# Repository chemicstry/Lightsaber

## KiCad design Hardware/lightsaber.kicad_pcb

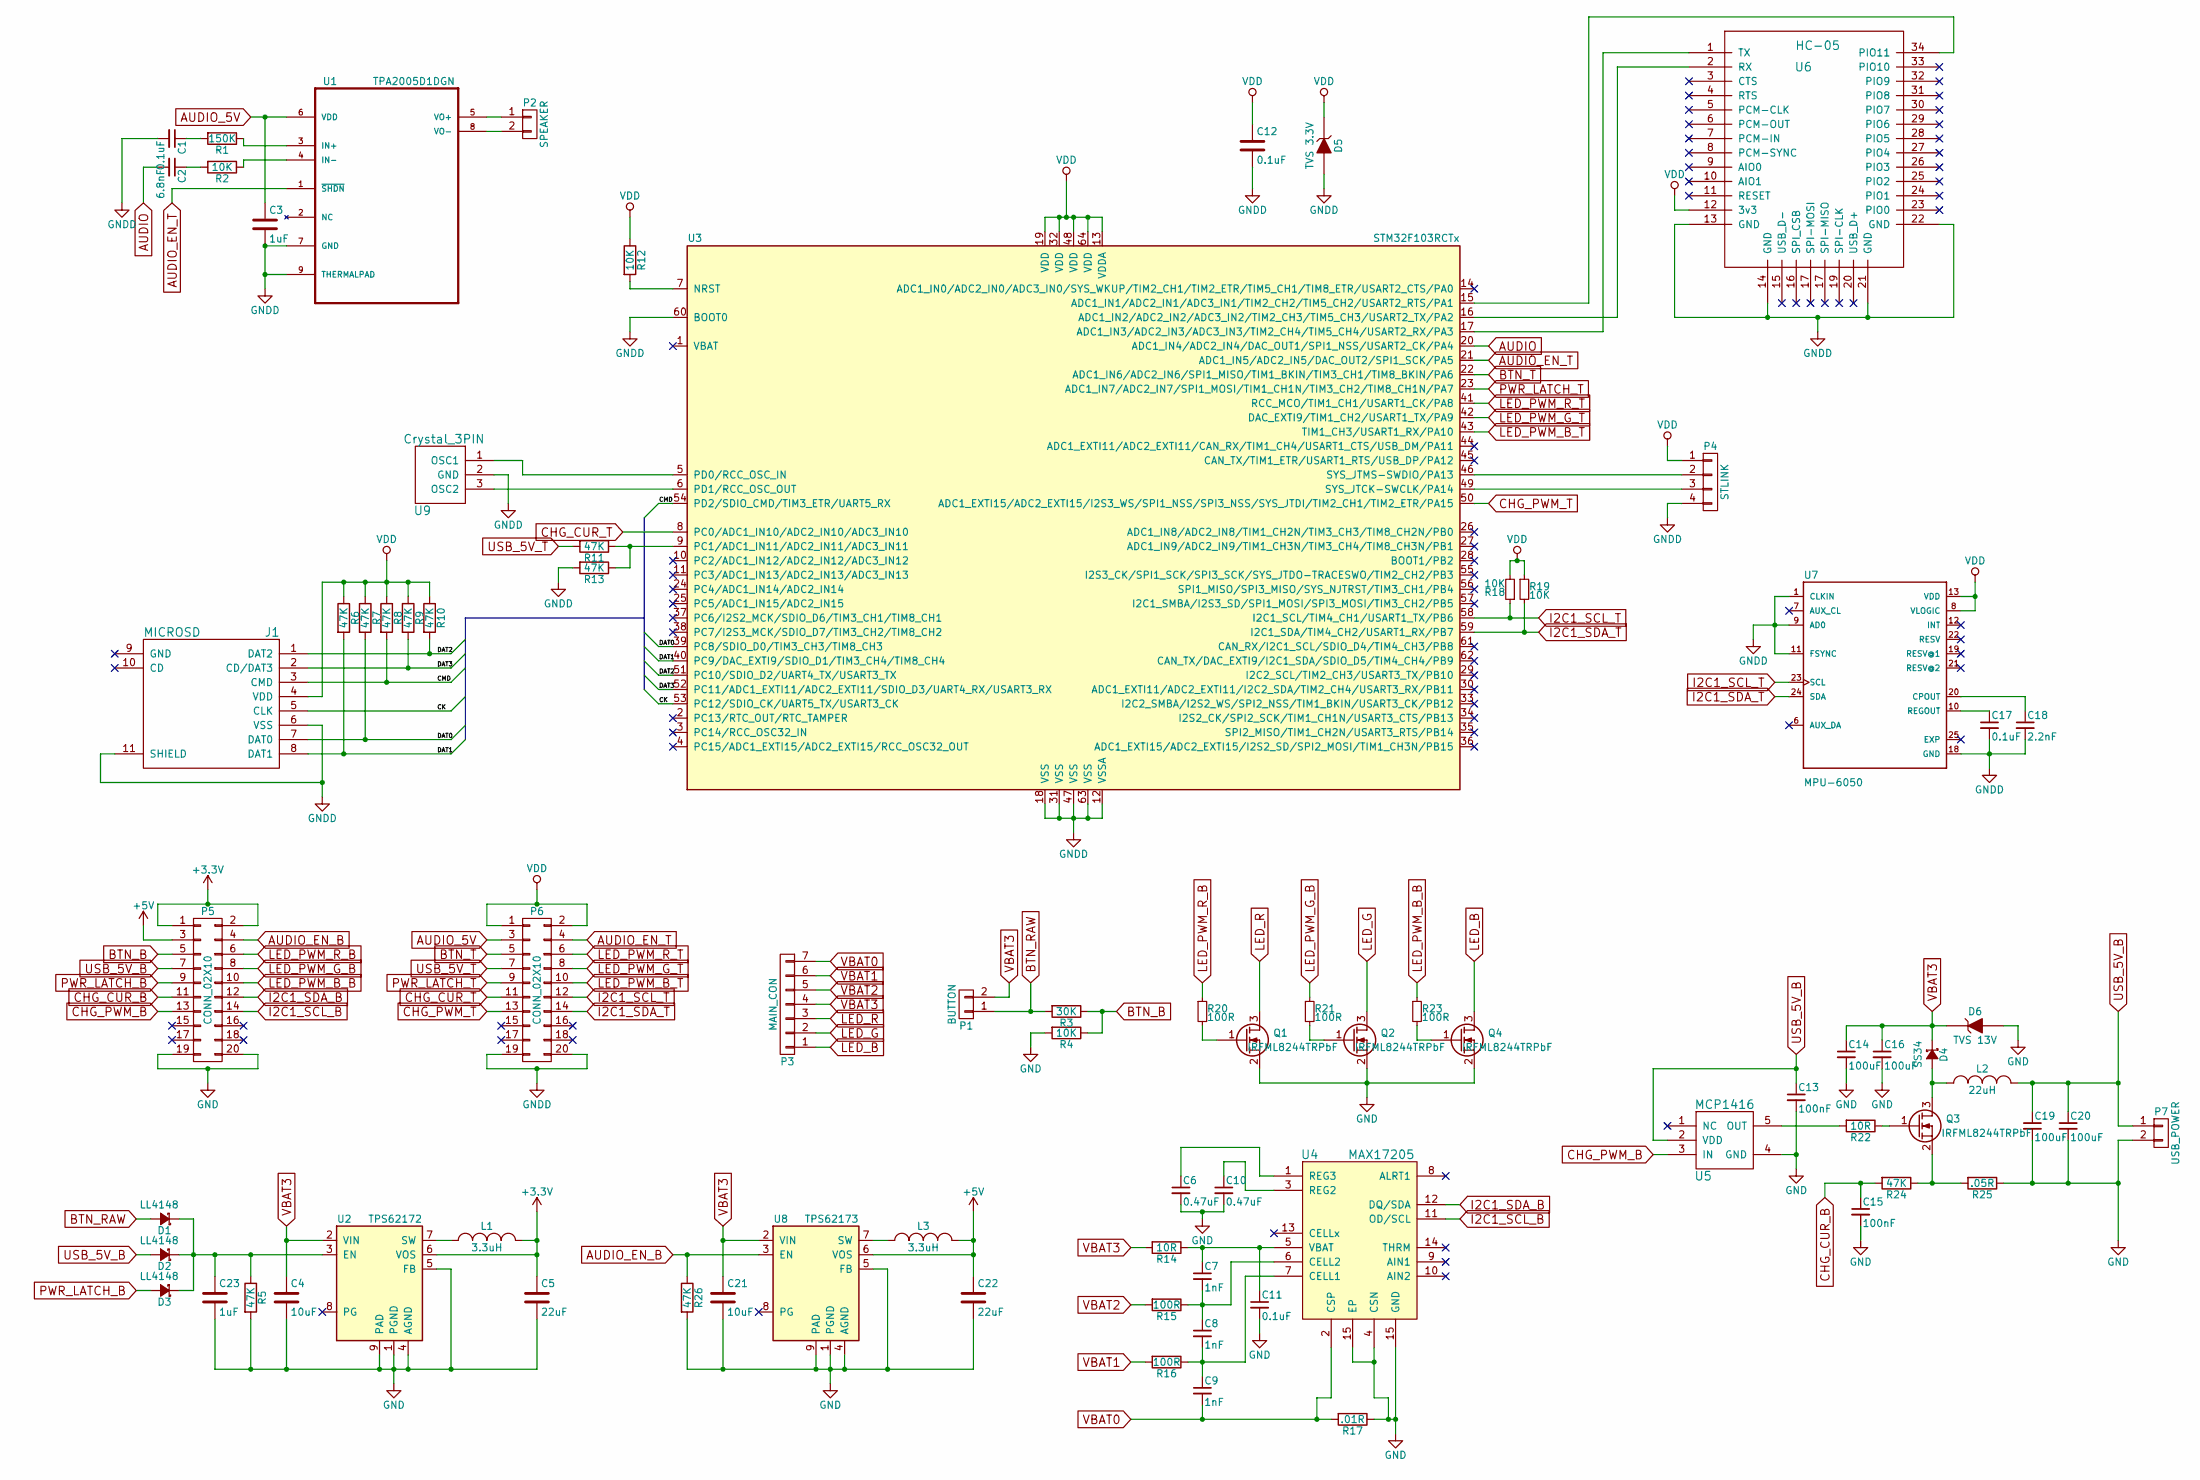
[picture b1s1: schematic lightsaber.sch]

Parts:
C1, C11, C12, C17: 0.1uF; C_0805_HandSoldering
C2: 6.8nF; C_0805_HandSoldering
C3, C23: 1uF; C_0805_HandSoldering
C4, C21: 10uF; C_0805_HandSoldering
C5, C22: 22uF; C_0805_HandSoldering
C6, C10: 0.47uF; C_0805_HandSoldering
C7, C8, C9: 1nF; C_0805_HandSoldering
C13, C15: 100nF; C_0805_HandSoldering
C14, C16, C19, C20: 100uF; C_1206_HandSoldering
C18: 2.2nF; C_0805_HandSoldering
D1, D2, D3: LL4148; SOD-80
D4: SS34; SMA-SMB_Universal_Handsoldering
D5: TVS 3.3V; D_SMB_Handsoldering
D6: TVS 13V; D_SMB_Handsoldering
J1: MICROSD; SD_CARD-112l-TXAO-R
L1, L3: 3.3uH; CD32
L2: 22uH; CD127
P1: BUTTON; JST_SH_SM02B-SRSS-TB_02x1.00mm_Angled
P2: SPEAKER; JST_SH_SM02B-SRSS-TB_02x1.00mm_Angled
P3: MAIN_CON; Pin_Header_Straight_1x07
P4: STLINK; JST_SH_BM04B-SRSS-TB_04x1.00mm_Straight
P5: CONN_02X10; PIN_HEADER_2x10_SMD_FEMALE
P6: CONN_02X10; PIN_HEADER_2x10_SMD_MALE
P7: USB_POWER; JST_PH_S2B-PH-K_02x2.00mm_Angled
Q1, Q2, Q3, Q4: IRFML8244TRPbF; SOT-23
R1: 150K; R_0805_HandSoldering
R2, R4, R12, R18, R19: 10K; R_0805_HandSoldering
R3: 30K; R_0805_HandSoldering
R5, R6, R7, R8, R9, R10, R11, R13, R24, R26: 47K; R_0805_HandSoldering
R14, R22: 10R; R_0805_HandSoldering
R15, R16, R20, R21, R23: 100R; R_0805_HandSoldering
R17: .01R; R_1206_HandSoldering
R25: .05R; R_1206_HandSoldering
U1: TPA2005D1DGN; SOP65P488X107-9N
U2: TPS62172; WSON8
U3: STM32F103RCTx; LQFP-64_10x10mm_Pitch0.5mm
U4: MAX17205; TDFN-14-1EP_3x3mm_Pitch0.4mm
U5: MCP1416; SOT-23-5
U6: HC-05
U7: MPU-6050; QFN50P400X400X95-25N
U8: TPS62173; WSON8
U9: Crystal_3PIN; Murata_CSTCE

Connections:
+3V3: C5.1, L1.2, P5.1, P5.2, U2.6 (VOS)
+5V: C22.1, L3.2, P5.3, U8.6 (VOS)
/CK: J1.5 (CLK), U3.53 (PC12/SDIO_CK/UART5_TX/USART3_CK)
/CMD: J1.3 (CMD), R8.2, U3.54 (PD2/SDIO_CMD/TIM3_ETR/UART5_RX)
/DAT0: J1.7 (DAT0), R7.2, U3.39 (PC8/SDIO_D0/TIM3_CH3/TIM8_CH3)
/DAT1: J1.8 (DAT1), R6.2, U3.40 (PC9/DAC_EXTI9/SDIO_D1/TIM3_CH4/TIM8_CH4)
/DAT2: J1.1 (DAT2), R10.2, U3.51 (PC10/SDIO_D2/UART4_TX/USART3_TX)
/DAT3: J1.2 (CD/DAT3), R9.2, U3.52 (PC11/ADC1_EXTI11/ADC2_EXTI11/SDIO_D3/UA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)
AUDIO: C2.2, U3.20 (ADC1_IN4/ADC2_IN4/DAC_OUT1/SPI1_NSS/USA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)
AUDIO_5V: C3.1, P6.3, U1.6 (VDD)
AUDIO_EN_B: P5.4, R26.1, U8.3 (EN)
AUDIO_EN_T: P6.4, U1.1 (~SHDN), U3.21 (ADC1_IN5/ADC2_IN5/DAC_OUT2/SPI1_SCK/PA5)
BTN_B: P5.5, R3.1, R4.1
BTN_RAW: D1.2 (A), P1.1, R3.2
BTN_T: P6.5, U3.22 (ADC1_IN6/ADC2_IN6/SPI1_MISO/TIM1_BKIN/T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)
CHG_CUR_B: C15.1, P5.11, R24.2
CHG_CUR_T: P6.11, U3.8 (PC0/ADC1_IN10/ADC2_IN10/ADC3_IN10)
CHG_PWM_B: P5.13, U5.3 (IN)
CHG_PWM_T: P6.13, U3.50 (ADC1_EXTI15/ADC2_EXTI15/I2S3_WS/SPI1_NS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)
GND: C4.2, C5.2, C6.2, C10.2, C11.2, C13.2, C14.2, C15.2, C16.2, C19.2, C20.2, C21.2, C22.2, C23.2, D6.2 (A), P5.19, P5.20, P7.2, Q1.2 (S), Q2.2 (S), Q4.2 (S), R4.2, R5.2, R17.1, R25.1, R26.2, U2.1 (PGND), U2.4 (AGND), U2.5 (FB), U2.9 (PAD), U4.4 (CSN), U4.15 (EP), U5.4 (GND), U8.1 (PGND), U8.4 (AGND), U8.5 (FB), U8.9 (PAD)
GNDD: C1.2, C3.2, C12.2, C17.2, C18.2, D5.2 (A), J1.6 (VSS), J1.11 (SHIELD), P4.4, P6.19, P6.20, R13.2, U1.7 (GND), U1.9 (THERMALPAD), U3.12 (VSSA), U3.18 (VSS), U3.31 (VSS), U3.47 (VSS), U3.60 (BOOT0), U3.63 (VSS), U6.13 (GND), U6.14 (GND), U6.21 (GND), U6.22 (GND), U7.1 (CLKIN), U7.9 (AD0), U7.11 (FSYNC), U7.18 (GND), U9.2 (GND)
I2C1_SCL_B: P5.14, U4.11 (OD/SCL)
I2C1_SCL_T: P6.12, R18.1, U3.58 (I2C1_SCL/TIM4_CH1/USART1_TX/PB6), U7.23 (SCL)
I2C1_SDA_B: P5.12, U4.12 (DQ/SDA)
I2C1_SDA_T: P6.14, R19.2, U3.59 (I2C1_SDA/TIM4_CH2/USART1_RX/PB7), U7.24 (SDA)
LED_B: P3.1, Q4.3 (D)
LED_G: P3.2, Q2.3 (D)
LED_PWM_B_B: P5.10, R23.1
LED_PWM_B_T: P6.10, U3.43 (TIM1_CH3/USART1_RX/PA10)
LED_PWM_G_B: P5.8, R21.1
LED_PWM_G_T: P6.8, U3.42 (DAC_EXTI9/TIM1_CH2/USART1_TX/PA9)
LED_PWM_R_B: P5.6, R20.1
LED_PWM_R_T: P6.6, U3.41 (RCC_MCO/TIM1_CH1/USART1_CK/PA8)
LED_R: P3.3, Q1.3 (D)
unnamed: C1.1, R1.2
unnamed: C2.1, R2.2
unnamed: C6.1, U4.1 (REG3)
unnamed: C7.2, C8.1, R15.1, U4.6 (CELL2)
unnamed: C8.2, C9.1, R16.1, U4.7 (CELL1)
unnamed: C10.1, U4.3 (REG2)
unnamed: C7.1, C11.1, R14.1, U4.5 (VBAT)
unnamed: C17.1, U7.10 (REGOUT)
unnamed: C18.1, U7.20 (CPOUT)
unnamed: C23.1, D1.1 (K), D2.1 (K), D3.1 (K), R5.1, U2.3 (EN)
unnamed: D4.2 (A), L2.1, Q3.3 (D)
unnamed: L1.1, U2.7 (SW)
unnamed: L3.1, U8.7 (SW)
unnamed: P2.1, U1.5 (VO+)
unnamed: P2.2, U1.8 (VO-)
unnamed: P4.2, U3.46 (SYS_JTMS-SWDIO/PA13)
unnamed: P4.3, U3.49 (SYS_JTCK-SWCLK/PA14)
unnamed: Q1.1 (G), R20.2
unnamed: Q2.1 (G), R21.2
unnamed: Q3.1 (G), R22.1
unnamed: Q3.2 (S), R24.1, R25.2
unnamed: Q4.1 (G), R23.2
unnamed: R1.1, U1.3 (IN+)
unnamed: R2.1, U1.4 (IN-)
unnamed: R11.1, R13.1, U3.9 (PC1/ADC1_IN11/ADC2_IN11/ADC3_IN11)
unnamed: R12.2, U3.7 (NRST)
unnamed: R22.2, U5.5 (OUT)
unnamed: U3.5 (PD0/RCC_OSC_IN), U9.1 (OSC1)
unnamed: U3.6 (PD1/RCC_OSC_OUT), U9.3 (OSC2)
unnamed: U3.15 (ADC1_IN1/ADC2_IN1/ADC3_IN1/TIM2_CH2/TIM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), U6.34 (PIO11)
unnamed: U3.16 (ADC1_IN2/ADC2_IN2/ADC3_IN2/TIM2_CH3/TIM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), U6.2 (RX)
unnamed: U3.17 (ADC1_IN3/ADC2_IN3/ADC3_IN3/TIM2_CH4/TIM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), U6.1 (TX)
PWR_LATCH_B: D3.2 (A), P5.9
PWR_LATCH_T: P6.9, U3.23 (ADC1_IN7/ADC2_IN7/SPI1_MOSI/TIM1_CH1N/T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)
USB_5V_B: C13.1, C19.1, C20.1, D2.2 (A), L2.2, P5.7, P7.1, U5.2 (VDD)
USB_5V_T: P6.7, R11.2
VBAT0: C9.2, P3.7, R17.2, U4.2 (CSP)
VBAT1: P3.6, R16.2
VBAT2: P3.5, R15.2
VBAT3: C4.1, C14.1, C16.1, C21.1, D4.1 (K), D6.1 (K), P1.2, P3.4, R14.2, U2.2 (VIN), U8.2 (VIN)
VDD: C12.1, D5.1 (K), J1.4 (VDD), P4.1, P6.1, P6.2, R6.1, R7.1, R8.1, R9.1, R10.1, R12.1, R18.2, R19.1, U3.13 (VDDA), U3.19 (VDD), U3.32 (VDD), U3.48 (VDD), U3.64 (VDD), U6.12 (3v3), U7.8 (VLOGIC), U7.13 (VDD)

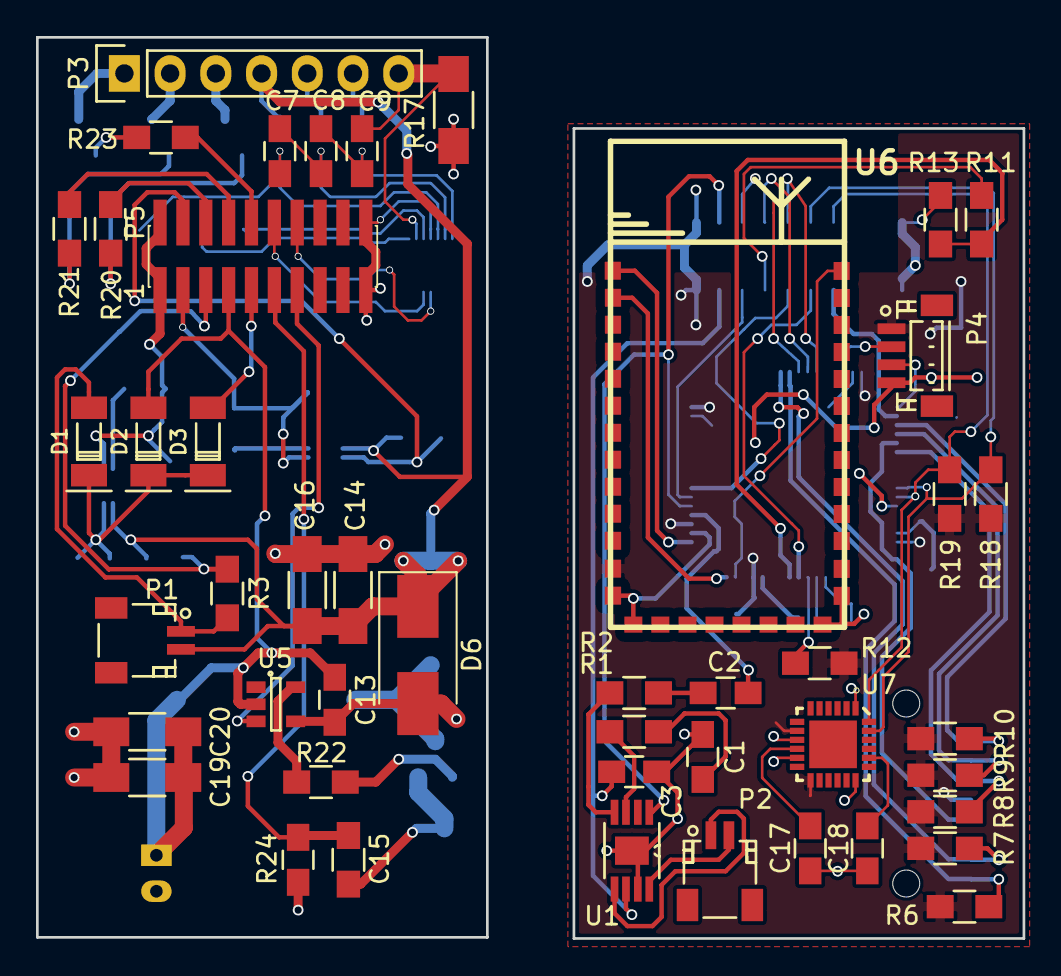
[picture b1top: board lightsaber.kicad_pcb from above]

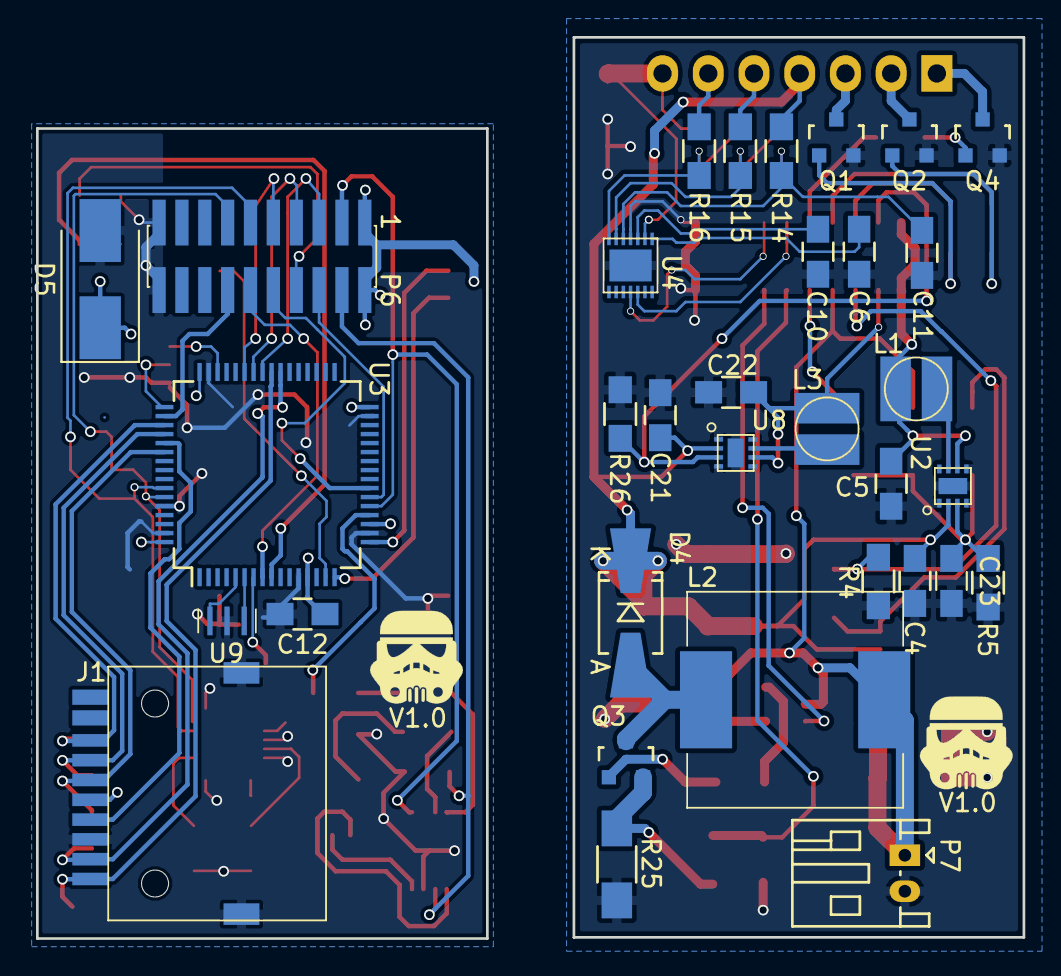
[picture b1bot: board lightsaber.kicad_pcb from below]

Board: 2 copper layers, 54.8 x 50.1 mm, 79 parts (33 on the bottom side), 75 nets.

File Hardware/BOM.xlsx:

Id | Designator | Package | Quantity | Designation | Supplier and ref | Qty | Bought Qty | Price | Price/board
1 | G***,G*** | stormtrooper | 2 | LOGO
2 | L2 | CD127 | 1 | 22uH | Aliexpress | 1 | 100 | 10 | 0.1
3 | C1,C11,C12,C17 | C_0805_HandSoldering | 4 | 0.1uF | Aliexpress | 4 | 1300 | 5.4 | 1.6615384615384615E-2
4 | C2 | C_0805_HandSoldering | 1 | 6.8nF | Aliexpress | 1 | 1300 | 5.4 | 4.1538461538461538E-3
5 | C3 | C_0805_HandSoldering | 1 | 1uF | Aliexpress | 1 | 1300 | 5.4 | 4.1538461538461538E-3
6 | C4,C21 | C_0805_HandSoldering | 2 | 10uF | Aliexpress | 2 | 100 | 1.82 | 3.6400000000000002E-2
7 | C5,C22 | C_0805_HandSoldering | 2 | 22uF | Aliexpress | 2 | 100 | 2.56 | 5.1200000000000002E-2
8 | C6,C10 | C_0805_HandSoldering | 2 | 0.47uF | Aliexpress | 2 | 1300 | 5.4 | 8.3076923076923076E-3
9 | C7,C8,C9 | C_0805_HandSoldering | 3 | 1nF | Aliexpress | 3 | 1300 | 5.4 | 1.2461538461538461E-2
10 | C13,C15 | C_0805_HandSoldering | 2 | 100nF | Aliexpress | 2 | 1300 | 5.4 | 8.3076923076923076E-3
11 | C14,C16,C19,C20 | C_1206_HandSoldering | 4 | 100uF | Aliexpress | 4 | 100 | 4.0999999999999996 | 0.16399999999999998
12 | C18 | C_0805_HandSoldering | 1 | 2.2nF | Aliexpress | 1 | 1300 | 5.4 | 4.1538461538461538E-3
13 | CON1 | SD_CARD-112l-TXAO-R | 1 | SD_Card | Aliexpress | 1 | 10 | 1.5 | 0.15
14 | D1,D2,D3,D4 | SMA-SMB_Universal_Handsoldering | 4 | SS34 | Aliexpress | 4 | 200 | 3.87 | 7.7399999999999997E-2
15 | L1,L3 | CD32 | 2 | 3.3uH | Aliexpress | 2 | 200 | 7 | 7.0000000000000007E-2
16 | P1 | JST_SH_SM02B-SRSS-TB_02x1.00mm_Angled | 1 | BUTTON | Aliexpress | 1 | 5 | 4.82 | 0.96400000000000008
17 | P2 | JST_SH_SM02B-SRSS-TB_02x1.00mm_Angled | 1 | SPEAKER | Aliexpress | 1 | 5 | 4.82 | 0.96400000000000008
18 | P3 | Pin_Header_Straight_1x07 | 1 | MAIN_CON | Aliexpress | 1 | 1 | 0 | 0
19 | P4 | JST_SH_BM04B-SRSS-TB_04x1.00mm_Straight | 1 | STLINK | Aliexpress | 1 | 10 | 2.99 | 0.29900000000000004
20 | P7 | JST_PH_S2B-PH-K_02x2.00mm_Angled | 1 | USB_POWER | Aliexpress | 1 | 5 | 4.82 | 0.96400000000000008
21 | Q1,Q2,Q3,Q4 | SOT-23 | 4 | IRFML8244TRPbF | Aliexpress | 4 | 30 | 4.99 | 0.66533333333333333
22 | R1 | R_0805_HandSoldering | 1 | 150K | Aliexpress | 1 | 100 | 0.42 | 4.1999999999999997E-3
23 | R2,R4,R12,R18,R19 | R_0805_HandSoldering | 5 | 10K | Aliexpress | 5 | 100 | 0.42 | 2.0999999999999998E-2
24 | R3 | R_0805_HandSoldering | 1 | 30K | Aliexpress | 1 | 100 | 0.42 | 4.1999999999999997E-3
25 | R5,R6,R7,R8,R9,R10,R11,R13,R24,R26 | R_0805_HandSoldering | 10 | 47K | Aliexpress | 10 | 100 | 0.42 | 4.1999999999999996E-2
26 | R14,R22 | R_0805_HandSoldering | 2 | 10R | Aliexpress | 2 | 100 | 0.42 | 8.3999999999999995E-3
27 | R15,R16,R20,R21,R23 | R_0805_HandSoldering | 5 | 100R | Aliexpress | 5 | 100 | 0.42 | 2.0999999999999998E-2
28 | R17 | R_1206_HandSoldering | 1 | .01R | Aliexpress | 1 | 100 | 1.96 | 1.9599999999999999E-2
29 | R25 | R_1206_HandSoldering | 1 | .05R | Aliexpress | 1 | 100 | 1.55 | 1.55E-2
30 | U1 | SOP65P488X107-9N | 1 | TPA2005D1DGN | Aliexpress | 1 | 5 | 3.81 | 0.76200000000000001
31 | U2 | S-PWSON-N8 | 1 | TPS62172 | Lemona | 1 | 4 | 4.04 | 1.01
32 | U3 | LQFP-64_10x10mm_Pitch0.5mm | 1 | STM32F103RCTx | Aliexpress | 1 | 5 | 11.55 | 2.31
33 | U4 | TDFN-14-1EP_3x3mm_Pitch0.4mm | 1 | MAX17205 | Farnell | 1 | 4 | 17.48 | 4.37
34 | U5 | SOT-23-5 | 1 | IRS44273L | Farnell | 1 | 5 | 3.56 | 0.71199999999999997
35 | U6 | HC-05 | 1 | HC-05 | Ebay | 1 | 5 | 13.89 | 2.778
36 | U7 | QFN50P400X400X95-25N | 1 | MPU-6050 | Aliexpress | 1 | 10 | 13.74 | 1.3740000000000001
37 | U8 | S-PWSON-N8 | 1 | TPS62173 | Lemona | 1 | 4 | 4.5199999999999996 | 1.1299999999999999
38 | P5 | PIN_HEADER_2x10_SMD_FEMALE | 1 | CONN_02X10 | Aliexpress | 1 | 5 | 1.46 | 0.29199999999999998
39 | P6 | PIN_HEADER_2x10_SMD_MALE | 1 | CONN_02X10 | Aliexpress | 1 | 5 | 1.46 | 0.29199999999999998
 |  |  |  |  |  |  | Total: | 172.63000000000002 | 19.72938717948718

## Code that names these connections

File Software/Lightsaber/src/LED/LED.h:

#ifndef _LED_H_
#define _LED_H_

#include "stm32f10x.h"
#include "RGBConverter.h"

#include <functional>

#define LED_TIMER TIM1
#define LED_TIMER_PERIPH RCC_APB2Periph_TIM1
#define LED_PORT GPIOA
#define LED_PORT_PERIPH RCC_APB2Periph_GPIOA
#define LED_R_PIN GPIO_Pin_8
#define LED_G_PIN GPIO_Pin_9
#define LED_B_PIN GPIO_Pin_10

typedef std::function<void()> BlinkCB;

class Color
{
public:
	virtual ~Color() {};
	virtual void GetRGB(uint8_t rgb[]) const = 0;
	virtual Color* Copy() const = 0;
};

class RGB : public Color
{
public:
	RGB(uint8_t _r = 0, uint8_t _g = 0, uint8_t _b = 0): r(_r), g(_g), b(_b) {}

	void GetRGB(uint8_t rgb[]) const
	{
		rgb[0] = r;
		rgb[1] = g;
		rgb[2] = b;
	}

	Color* Copy() const
	{
		return new RGB(*this);
	}

	uint8_t r, g, b;
};

class HSL : public Color
{
public:
	HSL(double _h = 0.0f, double _s = 0.0f, double _l = 0.0f): h(_h), s(_s), l(_l) {}

	void GetRGB(uint8_t rgb[]) const
	{
		RGBConverter::hslToRgb(h, s, l, rgb);
	}

	Color* Copy() const
	{
		return new HSL(*this);
	}

	double h, s, l;
};

class LED
{
public:
    void Init();
    void Set(const Color& color, bool force = false);
    void Set(const uint8_t rgb[]);

    void Blink(const Color& color, uint32_t count = 3, uint32_t delay = 200);
    void BlinkAsync(const Color& color, BlinkCB cb = nullptr, uint32_t count = 4, uint32_t delay = 100);

private:
    uint8_t _rgb[3];

    struct BlinkAsyncParams
    {
    	Color* 		color;
    	uint32_t 	count;
    	BlinkCB		cb;
    	uint32_t 	timer;
    } _blinkParams;
};

extern LED sLed;

#endif

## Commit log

2017-05-25 First push
